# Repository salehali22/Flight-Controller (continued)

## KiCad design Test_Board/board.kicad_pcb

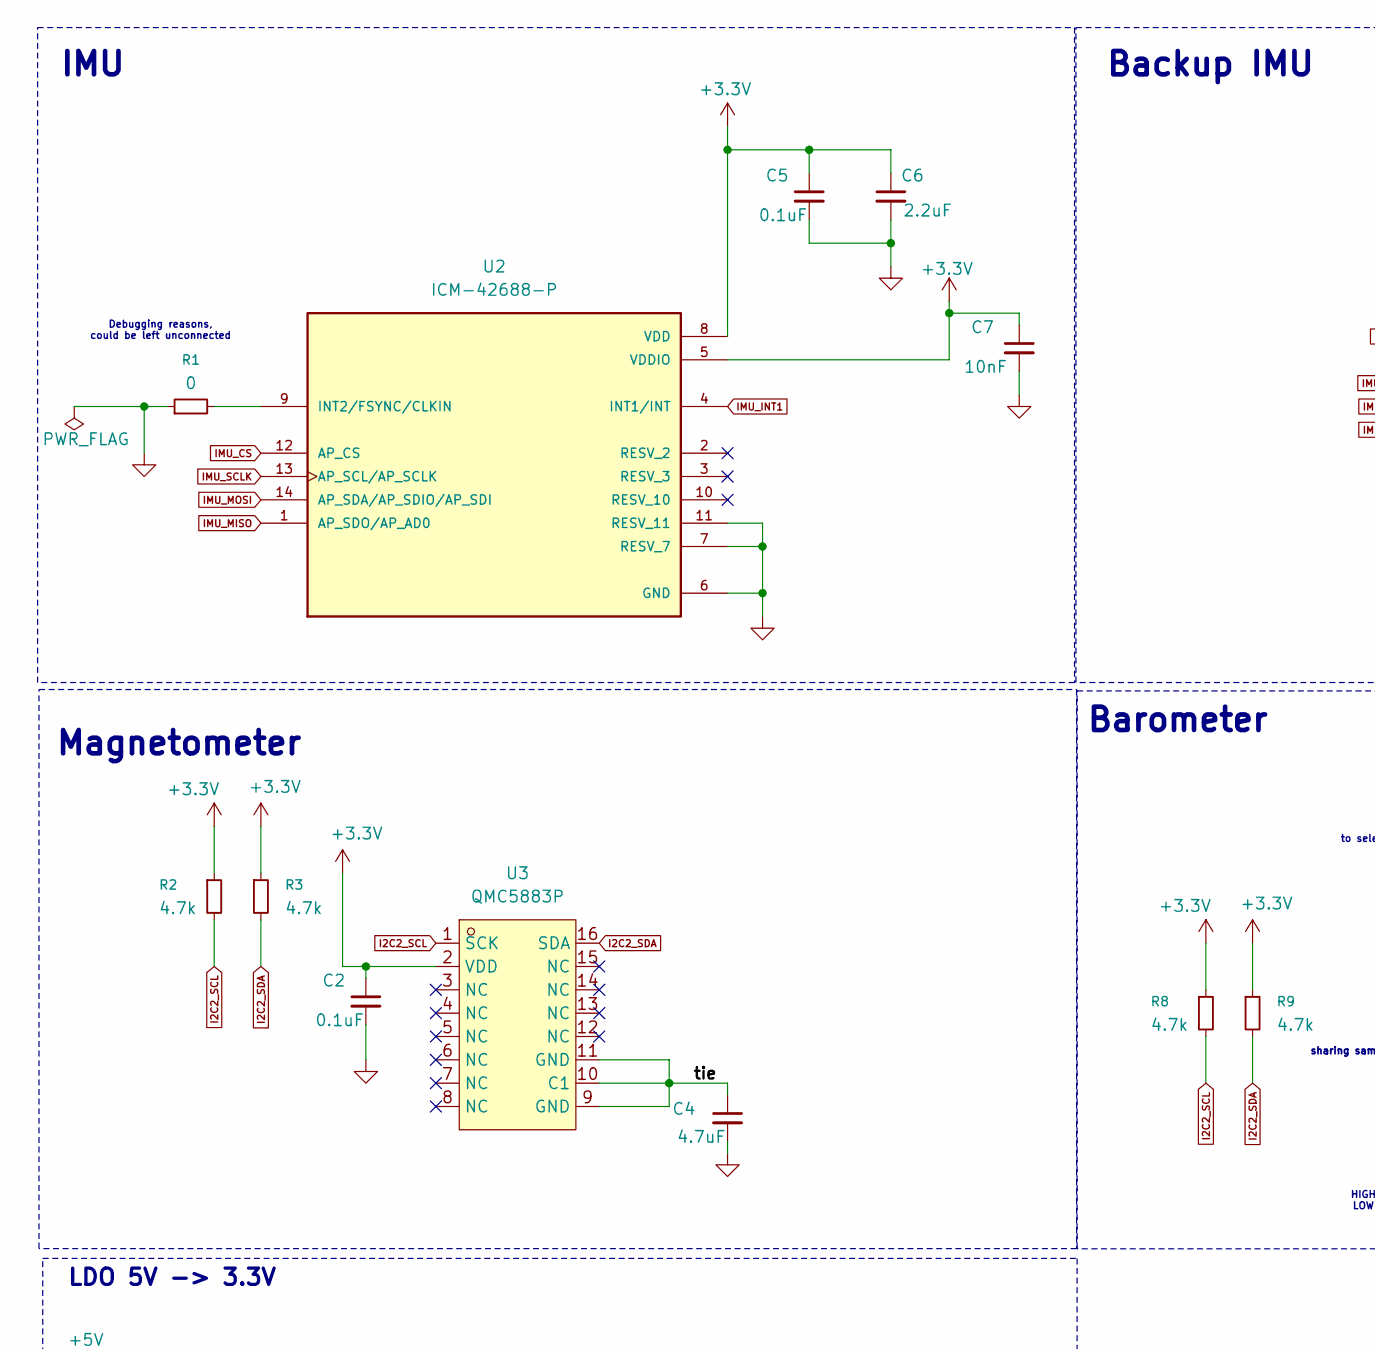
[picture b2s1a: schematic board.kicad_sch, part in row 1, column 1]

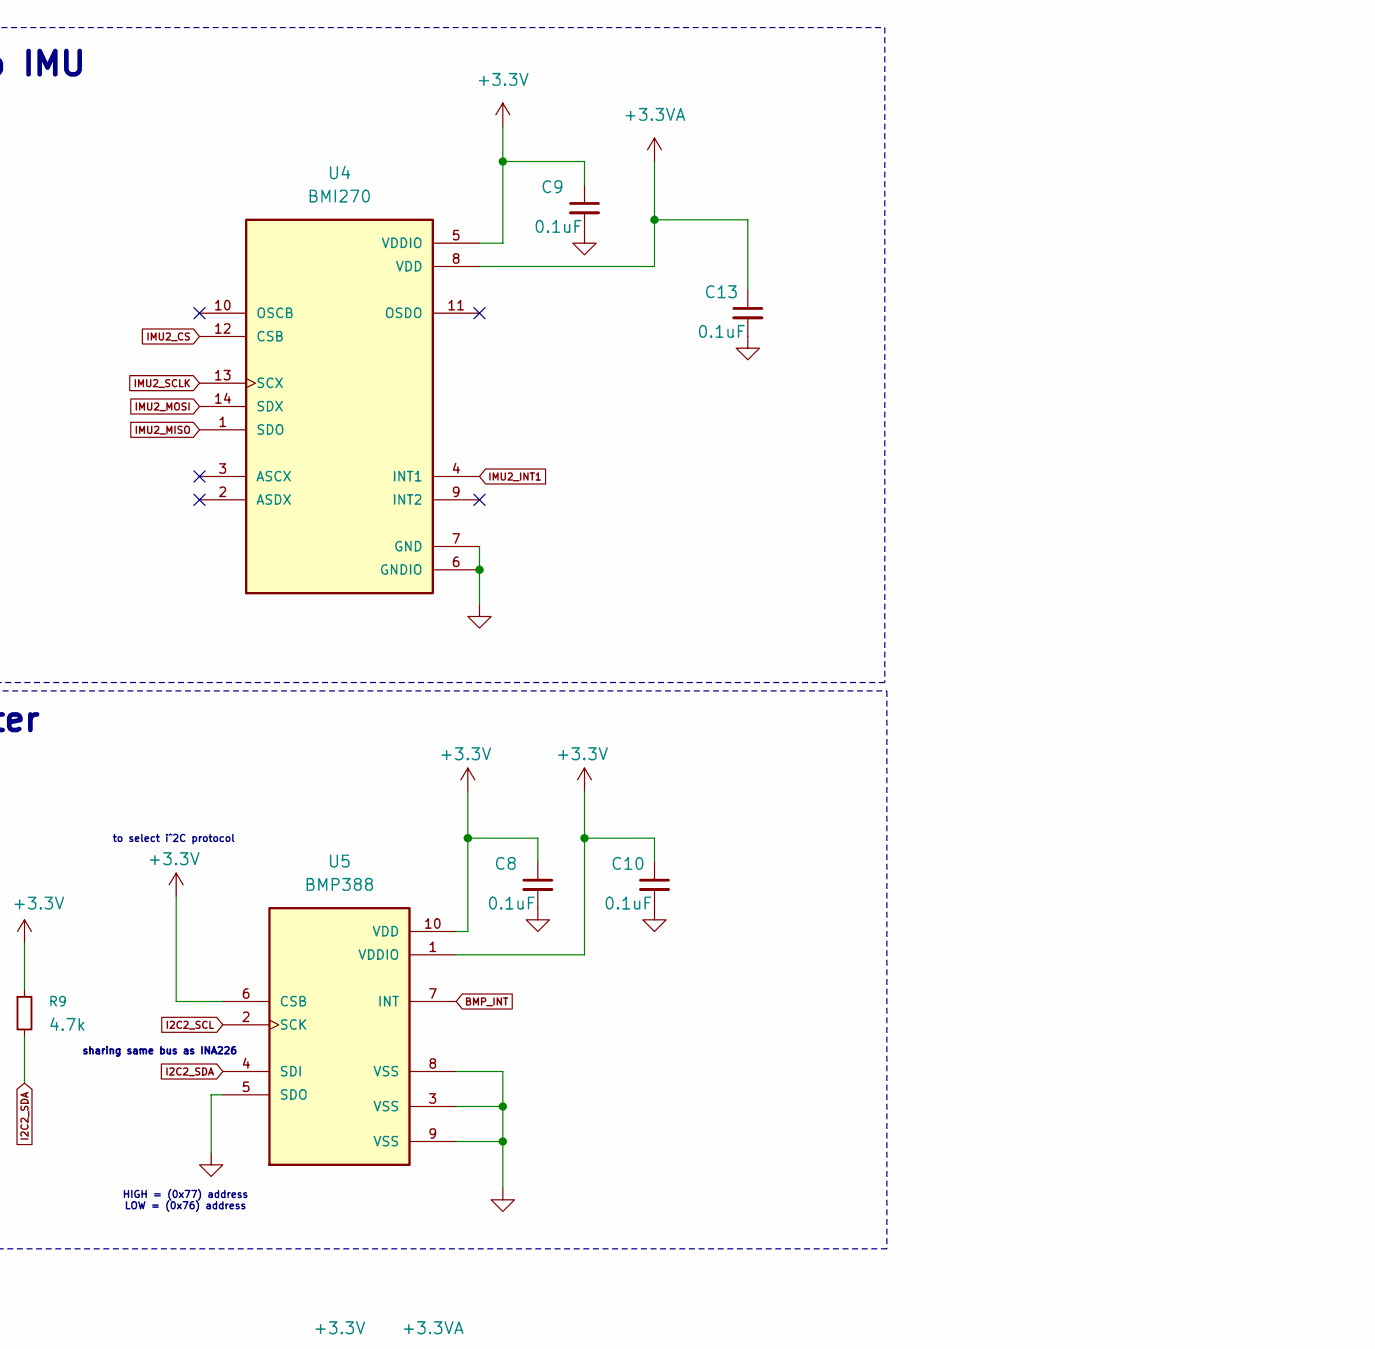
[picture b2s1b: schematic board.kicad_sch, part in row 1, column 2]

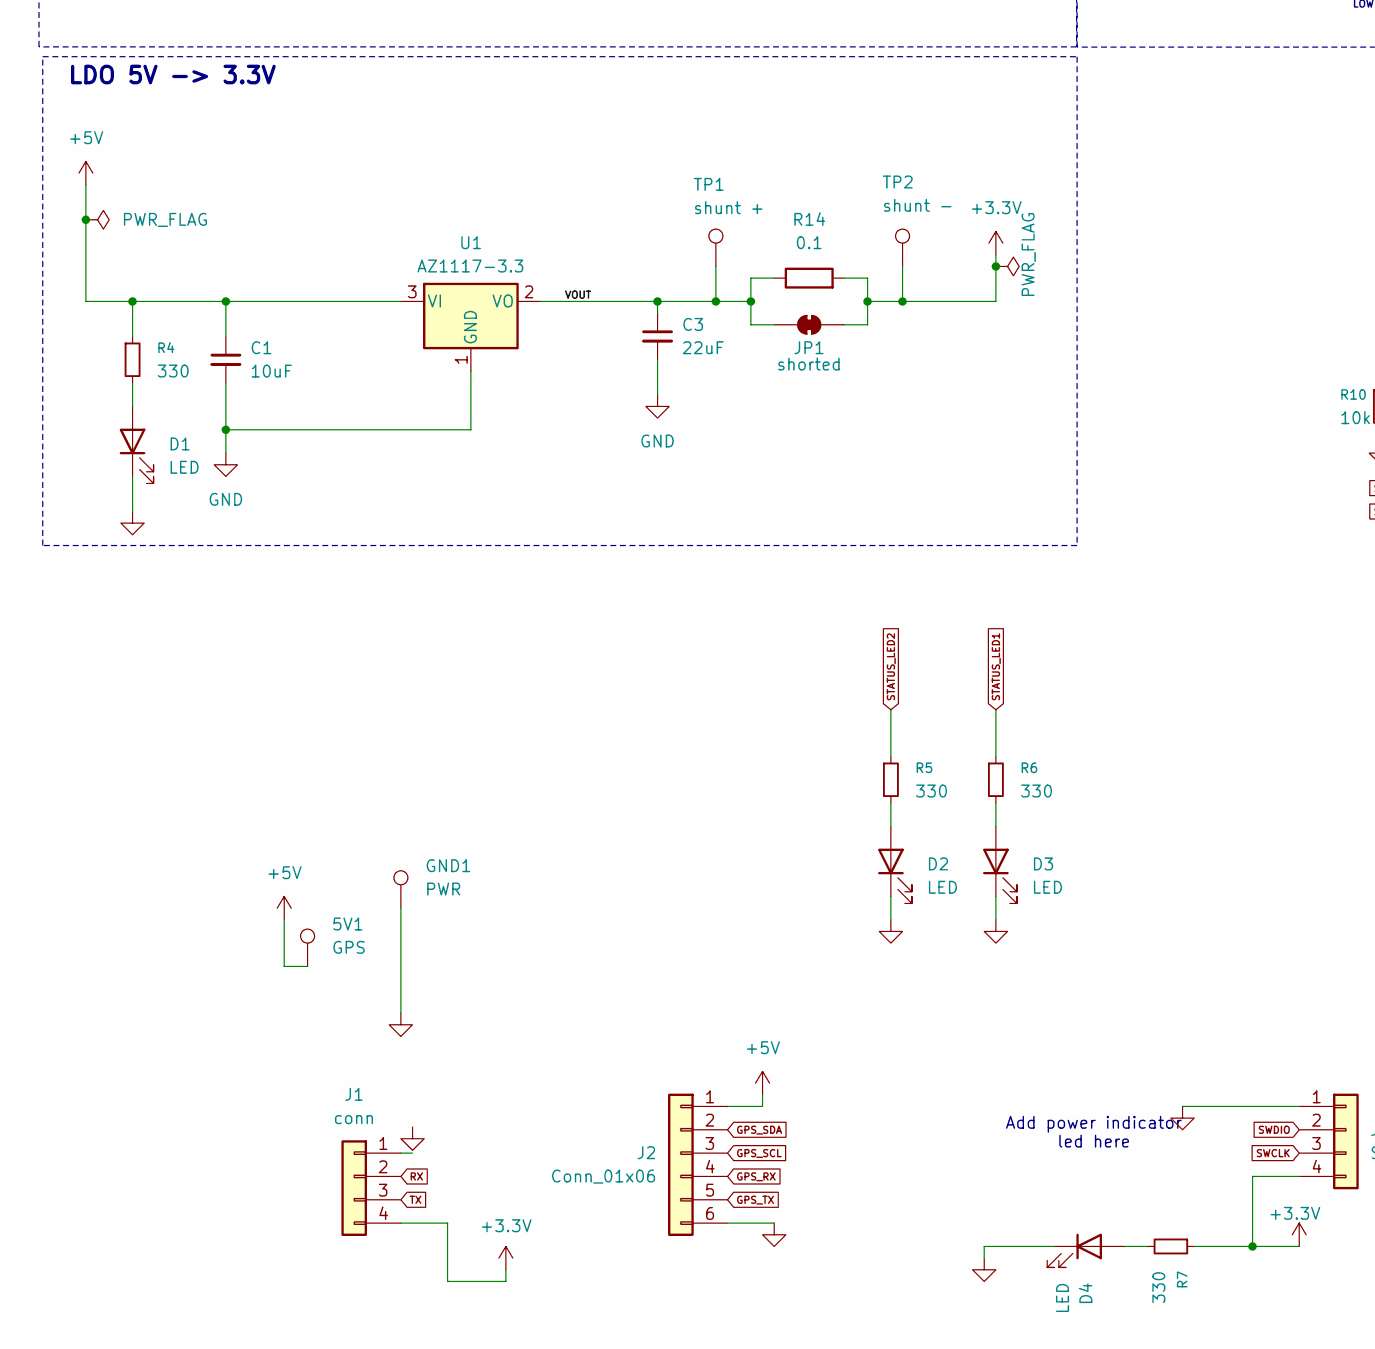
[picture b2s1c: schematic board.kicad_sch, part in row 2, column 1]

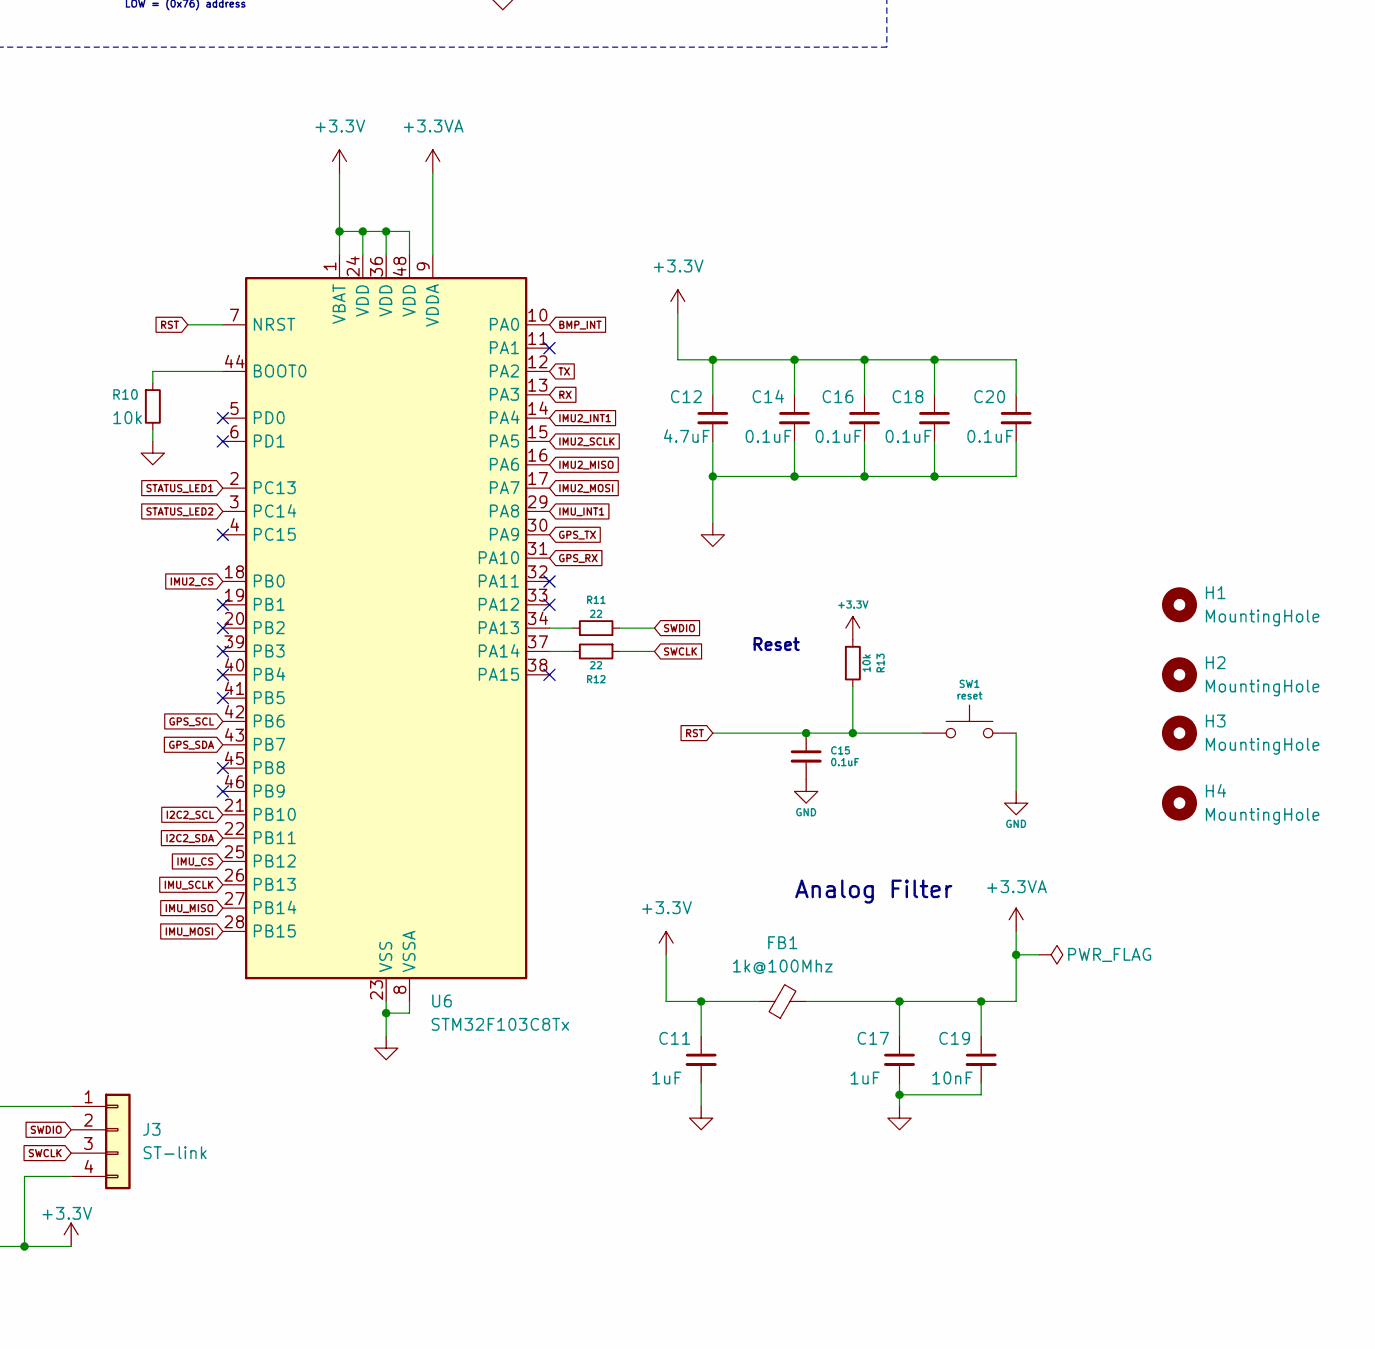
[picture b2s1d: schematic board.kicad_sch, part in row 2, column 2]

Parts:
5V1: GPS; Solderpad
C1: 10uF; C_0603_1608Metric; JLCPCB PART# C19702
C2, C5, C8, C9, C10, C13, C14, C15, C16, C18, C20: 0.1uF; C_0603_1608Metric; JLCPCB PART# C14663
C3: 22uF; C_0603_1608Metric; JLCPCB PART# C86295
C4, C12: 4.7uF; C_0603_1608Metric; JLCPCB PART# C1705
C6: 2.2uF; C_0603_1608Metric; JLCPCB PART# C23630
C7, C19: 10nF; C_0603_1608Metric; JLCPCB PART# C100042
C11, C17: 1uF; C_0603_1608Metric; JLCPCB PART# C15849
D1, D2, D3, D4: LED; LED_0805_2012Metric; JLCPCB PART# C20608785
FB1: 1k@100Mhz; L_0603_1608Metric; JLCPCB PART# C44838
GND1: PWR; Solderpad
H1, H2, H3, H4: MountingHole; MountingHole_2.2mm_M2_Pad_Via
J1: conn; JST_EH_B4B-EH-A_1x04_P2.50mm_Vertical
J2: Conn_01x06; PinHeader_1x06_P2.54mm_Vertical
J3: ST-link; PinHeader_1x04_P2.54mm_Horizontal
JP1: shorted; SolderJumper-2_P1.3mm_Bridged_Pad1.0x1.5mm
R1: 0; R_0603_1608Metric; JLCPCB PART# C95177
R2, R3, R8, R9: 4.7k; R_0603_1608Metric; JLCPCB PART# C2904521
R4, R5, R6, R7: 330; R_0603_1608Metric; JLCPCB PART# C105881
R10, R13: 10k; R_0603_1608Metric; JLCPCB PART# C98220
R11, R12: 22; R_0603_1608Metric; JLCPCB PART# C107701
R14: 0.1; R_2512_6332Metric_Pad1.40x3.35mm_HandSolder
SW1: reset; SW_Push_SPST_NO_Alps_SKRK; JLCPCB PART# C115357
TP1: shunt +; Solderpad
TP2: shunt -; Solderpad
U1: AZ1117-3.3; SOT-223; JLCPCB PART# C108495
U2: ICM-42688-P; PQFN50P300X250X97-14N; PARTREV 1.2
U3: QMC5883P; LCSC Part C2847467
U4: BMI270; XDCR_BMI270; JLCPCB PART# C2836813
U5: BMP388; PQFN50P200X200X80-10N; PARTREV 1.1; JLCPCB PART# C779278
U6: STM32F103C8Tx; LQFP-48_7x7mm_P0.5mm; JLCPCB PART# C8734

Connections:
+3.3V: C2.1, C5.1, C6.1, C7.1, C8.1, C9.1, C10.1, C11.1, C12.1, C14.1, C16.1, C18.1, C20.1, FB1.1, J1.4, J3.4, JP1.2 (B), R2.1, R3.1, R7.1, R8.1, R9.1, R13.1, R14.2, TP2.1, U2.5 (VDDIO), U2.8 (VDD), U3.2 (VDD), U4.5 (VDDIO), U5.1 (VDDIO), U5.6 (CSB), U5.10 (VDD), U6.1 (VBAT), U6.24 (VDD), U6.36 (VDD), U6.48 (VDD)
+3.3VA: C13.1, C17.1, C19.1, FB1.2, U4.8 (VDD), U6.9 (VDDA)
+5V: 5V1.1, C1.1, J2.1, R4.1, U1.3 (VI)
/VOUT: C3.1, JP1.1 (A), R14.1, TP1.1, U1.2 (VO)
/tie: C4.1, U3.9 (GND), U3.10 (C1), U3.11 (GND)
BMP_INT: U5.7 (INT), U6.10 (PA0)
GND: C1.2, C2.2, C3.2, C4.2, C5.2, C6.2, C7.2, C8.2, C9.2, C10.2, C11.2, C12.2, C13.2, C14.2, C15.2, C16.2, C17.2, C18.2, C19.2, C20.2, D1.1 (K), D2.1 (K), D3.1 (K), D4.1 (K), GND1.1, J2.6, J3.1, R1.1, R10.2, SW1.2, U1.1 (GND), U2.6 (GND), U2.7 (RESV_7), U2.11 (RESV_11), U4.6 (GNDIO), U4.7 (GND), U5.3 (VSS), U5.5 (SDO), U5.8 (VSS), U5.9 (VSS), U6.8 (VSSA), U6.23 (VSS), U6.35 (VSS), U6.47 (VSS)
GPS_RX: J2.4, U6.31 (PA10)
GPS_SCL: J2.3, U6.42 (PB6)
GPS_SDA: J2.2, U6.43 (PB7)
GPS_TX: J2.5, U6.30 (PA9)
I2C2_SCL: R2.2, R8.2, U3.1 (SCK), U5.2 (SCK), U6.21 (PB10)
I2C2_SDA: R3.2, R9.2, U3.16 (SDA), U5.4 (SDI), U6.22 (PB11)
IMU2_CS: U4.12 (CSB), U6.18 (PB0)
IMU2_INT1: U4.4 (INT1), U6.14 (PA4)
IMU2_MISO: U4.1 (SDO), U6.16 (PA6)
IMU2_MOSI: U4.14 (SDX), U6.17 (PA7)
IMU2_SCLK: U4.13 (SCX), U6.15 (PA5)
IMU_CS: U2.12 (AP_CS), U6.25 (PB12)
IMU_INT1: U2.4 (INT1/INT), U6.29 (PA8)
IMU_MISO: U2.1 (AP_SDO/AP_AD0), U6.27 (PB14)
IMU_MOSI: U2.14 (AP_SDA/AP_SDIO/AP_SDI), U6.28 (PB15)
IMU_SCLK: U2.13 (AP_SCL/AP_SCLK), U6.26 (PB13)
unnamed: D1.2 (A), R4.2
unnamed: D2.2 (A), R5.2
unnamed: D3.2 (A), R6.2
unnamed: D4.2 (A), R7.2
unnamed: R1.2, U2.9 (INT2/FSYNC/CLKIN)
unnamed: R10.1, U6.44 (BOOT0)
unnamed: R11.1, U6.34 (PA13)
unnamed: R12.2, U6.37 (PA14)
RST: C15.1, R13.2, SW1.1, U6.7 (NRST)
RX: J1.2, U6.13 (PA3)
STATUS_LED1: R6.1, U6.2 (PC13)
STATUS_LED2: R5.1, U6.3 (PC14)
SWCLK: J3.3, R12.1
SWDIO: J3.2, R11.2
TX: J1.3, U6.12 (PA2)

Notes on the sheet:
Analog Filter
Add power indicator led here
Backup IMU
Debugging reasons, could be left unconnected
to select i^2C protocol
Reset
Barometer
LDO 5V -> 3.3V
IMU
HIGH = (0x77) address LOW = (0x76) address
Magnetometer
sharing same bus as INA226

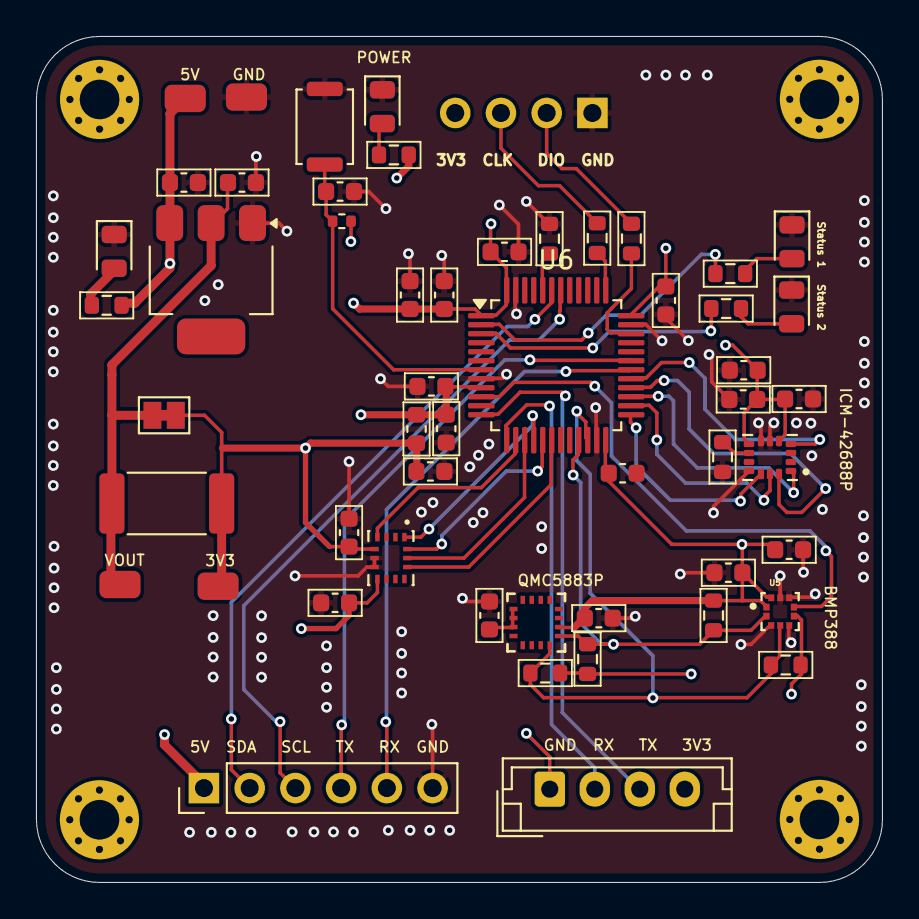
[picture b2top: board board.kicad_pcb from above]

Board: 4 copper layers, 47.0 x 47.0 mm, 58 parts (1 on the bottom side), 38 nets.

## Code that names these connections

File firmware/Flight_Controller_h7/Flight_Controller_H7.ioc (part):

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Mcu.Name=STM32H743VITx
Mcu.Package=LQFP100
Mcu.UserName=STM32H743VITx
PA0.GPIOParameters=PinAttribute
PA0.Mode=Asynchronous
PA0.PinAttribute=Free
PA0.Signal=UART4_TX
PA1.GPIOParameters=GPIO_Label,PinAttribute
PA1.GPIO_Label=DJI_SBUS
PA1.Mode=Asynchronous
PA1.PinAttribute=Free
PA1.Signal=UART4_RX
PA11.GPIOParameters=PinAttribute
PA11.Mode=Device_Only
PA11.PinAttribute=Free
PA11.Signal=USB_OTG_FS_DM
PA12.GPIOParameters=PinAttribute
PA12.Mode=Device_Only
PA12.PinAttribute=Free
PA12.Signal=USB_OTG_FS_DP
PA13\ (JTMS/SWDIO).GPIOParameters=PinAttribute
PA13\ (JTMS/SWDIO).Mode=Serial_Wire
PA13\ (JTMS/SWDIO).PinAttribute=Free
PA13\ (JTMS/SWDIO).Signal=DEBUG_JTMS-SWDIO
PA14\ (JTCK/SWCLK).GPIOParameters=PinAttribute
PA14\ (JTCK/SWCLK).Mode=Serial_Wire
PA14\ (JTCK/SWCLK).PinAttribute=Free
PA14\ (JTCK/SWCLK).Signal=DEBUG_JTCK-SWCLK
PA2.GPIOParameters=GPIO_Label,PinAttribute
PA2.GPIO_Label=VTX_TX
PA2.Mode=Asynchronous
PA2.PinAttribute=Free
PA2.Signal=USART2_TX
PA3.GPIOParameters=GPIO_Label,PinAttribute
PA3.GPIO_Label=VTX_RX
PA3.Mode=Asynchronous
PA3.PinAttribute=Free
PA3.Signal=USART2_RX
PA4.GPIOParameters=GPIO_Label,PinAttribute
PA4.GPIO_Label=FLASH_CS
PA4.PinAttribute=Free
PA4.Signal=GPIO_Output
PA5.GPIOParameters=GPIO_Label,PinAttribute
PA5.GPIO_Label=FLASH_SCK
PA5.Mode=Full_Duplex_Master
PA5.PinAttribute=Free
PA5.Signal=SPI1_SCK
PA6.GPIOParameters=GPIO_Label,PinAttribute
PA6.GPIO_Label=FLASH_MISO
PA6.Mode=Full_Duplex_Master
PA6.PinAttribute=Free
PA6.Signal=SPI1_MISO
PA7.GPIOParameters=GPIO_Label,PinAttribute
PA7.GPIO_Label=FLASH_MOSI
PA7.Mode=Full_Duplex_Master
PA7.PinAttribute=Free
PA7.Signal=SPI1_MOSI
PB0.GPIOParameters=PinState,GPIO_Label,PinAttribute
PB0.GPIO_Label=STATUS_LED_1
PB0.PinAttribute=Free
PB0.PinState=GPIO_PIN_SET
PB0.Signal=GPIO_Output
PB1.GPIOParameters=GPIO_Label,PinAttribute
PB1.GPIO_Label=BMP_INT1
PB1.PinAttribute=Free
PB1.Signal=GPXTI1
PB10.GPIOParameters=PinAttribute
PB10.Mode=I2C
PB10.PinAttribute=Free
PB10.Signal=I2C2_SCL
PB11.GPIOParameters=PinAttribute
PB11.Mode=I2C
PB11.PinAttribute=Free
PB11.Signal=I2C2_SDA
PB12.GPIOParameters=GPIO_Label,PinAttribute
PB12.GPIO_Label=TELEMETRY_RX
PB12.Mode=Asynchronous
PB12.PinAttribute=Free
PB12.Signal=UART5_RX
PB13.GPIOParameters=GPIO_Label,PinAttribute
PB13.GPIO_Label=TELEMETRY_TX
PB13.Mode=Asynchronous
PB13.PinAttribute=Free
PB13.Signal=UART5_TX
PB14.GPIOParameters=GPIO_Label,PinAttribute
PB14.GPIO_Label=Expansion_TX
PB14.Mode=Asynchronous
PB14.PinAttribute=Free
PB14.Signal=USART1_TX
PB15.GPIOParameters=GPIO_Label,PinAttribute
PB15.GPIO_Label=Expansion_RX
PB15.Mode=Asynchronous
PB15.PinAttribute=Free
PB15.Signal=USART1_RX
PB3\ (JTDO/TRACESWO).GPIOParameters=GPIO_Label,PinAttribute
PB3\ (JTDO/TRACESWO).GPIO_Label=IMU2_SCLK
PB3\ (JTDO/TRACESWO).Mode=Full_Duplex_Master
PB3\ (JTDO/TRACESWO).PinAttribute=Free
PB3\ (JTDO/TRACESWO).Signal=SPI6_SCK
PB4\ (NJTRST).GPIOParameters=GPIO_Label,PinAttribute
PB4\ (NJTRST).GPIO_Label=IMU2_MISO
PB4\ (NJTRST).Mode=Full_Duplex_Master
PB4\ (NJTRST).PinAttribute=Free
PB4\ (NJTRST).Signal=SPI6_MISO
PB5.GPIOParameters=GPIO_Label,PinAttribute
PB5.GPIO_Label=IMU2_MOSI
PB5.Mode=Full_Duplex_Master
PB5.PinAttribute=Free
PB5.Signal=SPI6_MOSI
PB6.GPIOParameters=GPIO_Label,PinAttribute
PB6.GPIO_Label=GPS_SCL
PB6.Mode=I2C
PB6.PinAttribute=Free
PB6.Signal=I2C4_SCL
PB7.GPIOParameters=GPIO_Label,PinAttribute
PB7.GPIO_Label=GPS_SDA
PB7.Mode=I2C
PB7.PinAttribute=Free
PB7.Signal=I2C4_SDA
PB8.GPIOParameters=PinAttribute
PB8.Mode=I2C
PB8.PinAttribute=Free
PB8.Signal=I2C1_SCL
PB9.GPIOParameters=PinAttribute
PB9.Mode=I2C
PB9.PinAttribute=Free
PB9.Signal=I2C1_SDA
PC1.GPIOParameters=GPIO_Label,PinAttribute
PC1.GPIO_Label=ADC_VOLTAGE
PC1.PinAttribute=Free
PC1.Signal=ADCx_INP11
PC10.GPIOParameters=GPIO_Label,PinAttribute
PC10.GPIO_Label=IMU_SCLK
PC10.Mode=Full_Duplex_Master
PC10.PinAttribute=Free
PC10.Signal=SPI3_SCK
PC11.GPIOParameters=GPIO_Label,PinAttribute
PC11.GPIO_Label=IMU_MISO
PC11.Mode=Full_Duplex_Master
PC11.PinAttribute=Free
PC11.Signal=SPI3_MISO
PC12.GPIOParameters=GPIO_Label,PinAttribute
PC12.GPIO_Label=IMU_MOSI
PC12.Mode=Full_Duplex_Master
PC12.PinAttribute=Free
PC12.Signal=SPI3_MOSI
PC13.GPIOParameters=GPIO_Label,PinAttribute
PC13.GPIO_Label=OSD_CS
PC13.PinAttribute=Free
PC13.Signal=GPIO_Output
PC3_C.GPIOParameters=GPIO_Label,PinAttribute
PC3_C.GPIO_Label=ADC_CURR
PC3_C.Mode=IN1-Single-Ended
PC3_C.PinAttribute=Free
PC3_C.Signal=ADC3_INP1
PC5.GPIOParameters=PinState,GPIO_Label,PinAttribute
PC5.GPIO_Label=STATUS_LED_2
PC5.PinAttribute=Free
PC5.PinState=GPIO_PIN_SET
PC5.Signal=GPIO_Output
PC6.GPIOParameters=GPIO_Label,PinAttribute
PC6.GPIO_Label=M1
PC6.PinAttribute=Free
PC6.Signal=S_TIM8_CH1
PC7.GPIOParameters=GPIO_Label,PinAttribute
PC7.GPIO_Label=M2
PC7.PinAttribute=Free
PC7.Signal=S_TIM8_CH2
PC8.GPIOParameters=GPIO_Label,PinAttribute
PC8.GPIO_Label=M3
PC8.PinAttribute=Free
PC8.Signal=S_TIM8_CH3
PC9.GPIOParameters=GPIO_Label,PinAttribute
PC9.GPIO_Label=M4
PC9.PinAttribute=Free
PC9.Signal=S_TIM8_CH4
PD0.GPIOParameters=PinAttribute
PD0.Mode=FDCAN_Activate
PD0.PinAttribute=Free
PD0.Signal=FDCAN1_RX
PD1.GPIOParameters=PinAttribute
PD1.Mode=FDCAN_Activate
PD1.PinAttribute=Free
PD1.Signal=FDCAN1_TX
PD12.GPIOParameters=GPIO_Label,PinAttribute
PD12.GPIO_Label=S1
PD12.PinAttribute=Free
PD12.Signal=S_TIM4_CH1
PD13.GPIOParameters=GPIO_Label,PinAttribute
PD13.GPIO_Label=S2
PD13.PinAttribute=Free
PD13.Signal=S_TIM4_CH2
PD14.GPIOParameters=GPIO_Label,PinAttribute
PD14.GPIO_Label=S3
PD14.PinAttribute=Free
PD14.Signal=S_TIM4_CH3
PD15.GPIOParameters=GPIO_Label,PinAttribute
PD15.GPIO_Label=S4
PD15.PinAttribute=Free
PD15.Signal=S_TIM4_CH4
PD2.GPIOParameters=GPIO_Label,PinAttribute
PD2.GPIO_Label=IMU_INT1
PD2.PinAttribute=Free
PD2.Signal=GPXTI2
PD3.GPIOParameters=GPIO_Label,PinAttribute
PD3.GPIO_Label=IMU_CS
PD3.PinAttribute=Free
PD3.Signal=GPIO_Output
PD7.GPIOParameters=GPIO_Label,PinAttribute
PD7.GPIO_Label=IMU2_CS
PD7.PinAttribute=Free
PD7.Signal=GPIO_Output
PD8.GPIOParameters=GPIO_Label,PinAttribute
PD8.GPIO_Label=WIFI/RC_TX
PD8.Mode=Asynchronous
PD8.PinAttribute=Free
PD8.Signal=USART3_TX
PD9.GPIOParameters=GPIO_Label,PinAttribute
PD9.GPIO_Label=WIFI/RC_RX
PD9.Mode=Asynchronous
PD9.PinAttribute=Free
PD9.Signal=USART3_RX
PE0.GPIOParameters=GPIO_Label,PinAttribute
PE0.GPIO_Label=GPS_RX
PE0.Mode=Asynchronous
PE0.PinAttribute=Free
PE0.Signal=UART8_RX
PE1.GPIOParameters=GPIO_Label,PinAttribute
PE1.GPIO_Label=GPS_TX
PE1.Mode=Asynchronous
PE1.PinAttribute=Free
PE1.Signal=UART8_TX
PE11.GPIOParameters=GPIO_Label,PinAttribute
PE11.GPIO_Label=M6
PE11.PinAttribute=Free
PE11.Signal=S_TIM1_CH2
PE13.GPIOParameters=GPIO_Label,PinAttribute
PE13.GPIO_Label=M7
PE13.PinAttribute=Free
PE13.Signal=S_TIM1_CH3
PE14.GPIOParameters=GPIO_Label,PinAttribute
PE14.GPIO_Label=M8
PE14.PinAttribute=Free
PE14.Signal=S_TIM1_CH4
PE2.GPIOParameters=GPIO_Label,PinAttribute
PE2.GPIO_Label=OSD_SCK
PE2.Mode=Full_Duplex_Master
PE2.PinAttribute=Free
PE2.Signal=SPI4_SCK
PE4.GPIOParameters=GPIO_Label,PinAttribute
PE4.GPIO_Label=IMU2_INT
PE4.PinAttribute=Free
PE4.Signal=GPXTI4
PE5.GPIOParameters=GPIO_Label,PinAttribute
PE5.GPIO_Label=OSD_MISO
PE5.Mode=Full_Duplex_Master
PE5.PinAttribute=Free
PE5.Signal=SPI4_MISO
PE6.GPIOParameters=GPIO_Label,PinAttribute
PE6.GPIO_Label=OSD_MOSI
PE6.Mode=Full_Duplex_Master
PE6.PinAttribute=Free
PE6.Signal=SPI4_MOSI
PE7.GPIOParameters=GPIO_Label,PinAttribute
PE7.GPIO_Label=DJI_RX
PE7.Mode=Asynchronous
PE7.PinAttribute=Free
PE7.Signal=UART7_RX
PE8.GPIOParameters=GPIO_Label,PinAttribute
PE8.GPIO_Label=DJI_TX
PE8.Mode=Asynchronous
PE8.PinAttribute=Free
PE8.Signal=UART7_TX
PE9.GPIOParameters=GPIO_Label,PinAttribute
PE9.GPIO_Label=M5
PE9.PinAttribute=Free
PE9.Signal=S_TIM1_CH1
PH0-OSC_IN\ (PH0).GPIOParameters=PinAttribute
PH0-OSC_IN\ (PH0).Mode=HSE-External-Clock-Source
PH0-OSC_IN\ (PH0).PinAttribute=Free
PH0-OSC_IN\ (PH0).Signal=RCC_OSC_IN
RCC.HSE_VALUE=8000000
RCC.SYSCLKFreq_VALUE=240000000
RCC.SYSCLKSource=RCC_SYSCLKSOURCE_PLLCLK
board=custom

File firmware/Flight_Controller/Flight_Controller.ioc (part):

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Mcu.Name=STM32F722R(C-E)Tx
Mcu.Package=LQFP64
Mcu.UserName=STM32F722RETx
PA0-WKUP.GPIOParameters=GPIO_Label
PA0-WKUP.GPIO_Label=WIFI_TX
PA0-WKUP.Mode=Asynchronous
PA0-WKUP.Signal=UART4_TX
PA1.GPIOParameters=GPIO_Label
PA1.GPIO_Label=WIFI_RX
PA1.Mode=Asynchronous
PA1.Signal=UART4_RX
PA10.GPIOParameters=GPIO_Label
PA10.GPIO_Label=RC_Receiver_RX
PA10.Mode=Asynchronous
PA10.Signal=USART1_RX
PA11.Mode=Device_Only
PA11.Signal=USB_OTG_FS_DM
PA12.Mode=Device_Only
PA12.Signal=USB_OTG_FS_DP
PA13.Mode=Serial_Wire
PA13.Signal=SYS_JTMS-SWDIO
PA14.Mode=Serial_Wire
PA14.Signal=SYS_JTCK-SWCLK
PA2.GPIOParameters=GPIO_Label
PA2.GPIO_Label=GPS_TX
PA2.Mode=Asynchronous
PA2.Signal=USART2_TX
PA3.GPIOParameters=GPIO_Label
PA3.GPIO_Label=GPS_RX
PA3.Mode=Asynchronous
PA3.Signal=USART2_RX
PA4.GPIOParameters=GPIO_Label
PA4.GPIO_Label=IMU_CS
PA4.Signal=GPIO_Output
PA5.GPIOParameters=GPIO_Label
PA5.GPIO_Label=IMU_SCLK
PA5.Mode=Full_Duplex_Master
PA5.Signal=SPI1_SCK
PA6.GPIOParameters=GPIO_Label
PA6.GPIO_Label=IMU_MISO
PA6.Mode=Full_Duplex_Master
PA6.Signal=SPI1_MISO
PA7.GPIOParameters=GPIO_Label
PA7.GPIO_Label=IMU_MOSI
PA7.Mode=Full_Duplex_Master
PA7.Signal=SPI1_MOSI
PA8.GPIOParameters=GPIO_Label
PA8.GPIO_Label=GPS_SCL
PA8.Mode=I2C
PA8.Signal=I2C3_SCL
PA9.GPIOParameters=GPIO_Label
PA9.GPIO_Label=RC_Receiver_TX
PA9.Mode=Asynchronous
PA9.Signal=USART1_TX
PB0.GPIOParameters=GPIO_Label
PB0.GPIO_Label=ADC_Voltage
PB0.Signal=ADCx_IN8
PB1.GPIOParameters=GPIO_Label
PB1.GPIO_Label=SERVO_3
PB1.Signal=S_TIM3_CH4
PB10.GPIOParameters=GPIO_Label
PB10.GPIO_Label=I2C2_SCL
PB10.Mode=I2C
PB10.Signal=I2C2_SCL
PB11.GPIOParameters=GPIO_Label
PB11.GPIO_Label=I2C2_SDA
PB11.Mode=I2C
PB11.Signal=I2C2_SDA
PB12.GPIOParameters=GPIO_Label
PB12.GPIO_Label=OSD_CS
PB12.Signal=GPIO_Output
PB13.GPIOParameters=GPIO_Label
PB13.GPIO_Label=OSD_SCLK
PB13.Mode=Full_Duplex_Master
PB13.Signal=SPI2_SCK
PB14.GPIOParameters=GPIO_Label
PB14.GPIO_Label=SERVO_2
PB14.Signal=S_TIM12_CH1
PB15.GPIOParameters=GPIO_Label
PB15.GPIO_Label=SERVO_1
PB15.Signal=S_TIM12_CH2
PB2.GPIOParameters=GPIO_Label
PB2.GPIO_Label=FLASH_MOSI
PB2.Mode=Full_Duplex_Master
PB2.Signal=SPI3_MOSI
PB3.GPIOParameters=GPIO_Label
PB3.GPIO_Label=MOTOR_1
PB3.Signal=S_TIM2_CH2
PB4.GPIOParameters=GPIO_Label
PB4.GPIO_Label=MOTOR_2
PB4.Signal=S_TIM3_CH1
PB5.GPIOParameters=GPIO_Label
PB5.GPIO_Label=MOTOR_3
PB5.Signal=S_TIM3_CH2
PB6.GPIOParameters=GPIO_Label
PB6.GPIO_Label=MOTOR_4
PB6.Signal=S_TIM4_CH1
PB7.GPIOParameters=GPIO_Label
PB7.GPIO_Label=MOTOR_5
PB7.Signal=S_TIM4_CH2
PB8.GPIOParameters=GPIO_Label
PB8.GPIO_Label=QMC_SCL
PB8.Mode=I2C
PB8.Signal=I2C1_SCL
PB9.GPIOParameters=GPIO_Label
PB9.GPIO_Label=QMC_SDA
PB9.Mode=I2C
PB9.Signal=I2C1_SDA
PC0.GPIOParameters=GPIO_Label
PC0.GPIO_Label=STATUS_LED_3
PC0.Signal=GPIO_Output
PC1.GPIOParameters=GPIO_Label
PC1.GPIO_Label=OSD_MOSI
PC1.Mode=Full_Duplex_Master
PC1.Signal=SPI2_MOSI
PC10.GPIOParameters=GPIO_Label
PC10.GPIO_Label=FLASH_SCK
PC10.Mode=Full_Duplex_Master
PC10.Signal=SPI3_SCK
PC11.GPIOParameters=GPIO_Label
PC11.GPIO_Label=FLASH_MISO
PC11.Mode=Full_Duplex_Master
PC11.Signal=SPI3_MISO
PC12.GPIOParameters=GPIO_Label
PC12.GPIO_Label=FLASH_CS
PC12.Signal=GPIO_Output
PC13.GPIOParameters=GPIO_Label
PC13.GPIO_Label=INA226_ALERT
PC13.Signal=GPIO_Input
PC14-OSC32_IN.GPIOParameters=GPIO_Label
PC14-OSC32_IN.GPIO_Label=STATUS_LED_1
PC14-OSC32_IN.Signal=GPIO_Output
PC15-OSC32_OUT.GPIOParameters=GPIO_Label
PC15-OSC32_OUT.GPIO_Label=STATUS_LED_2
PC15-OSC32_OUT.Signal=GPIO_Output
PC2.GPIOParameters=GPIO_Label
PC2.GPIO_Label=OSD_MISO
PC2.Mode=Full_Duplex_Master
PC2.Signal=SPI2_MISO
PC3.GPIOParameters=GPIO_Label
PC3.GPIO_Label=BMP_INT
PC3.Signal=GPXTI3
PC6.GPIOParameters=GPIO_Label
PC6.GPIO_Label=Telemetry_TX
PC6.Mode=Asynchronous
PC6.Signal=USART6_TX
PC7.GPIOParameters=GPIO_Label
PC7.GPIO_Label=Telemetry_RX
PC7.Mode=Asynchronous
PC7.Signal=USART6_RX
PC8.GPIOParameters=GPIO_Label
PC8.GPIO_Label=IMU_INT
PC8.Signal=GPXTI8
PC9.GPIOParameters=GPIO_Label
PC9.GPIO_Label=GPS_SDA
PC9.Mode=I2C
PC9.Signal=I2C3_SDA
PH0-OSC_IN.Mode=HSE-External-Clock-Source
PH0-OSC_IN.Signal=RCC_OSC_IN
PH1-OSC_OUT.Mode=HSE-External-Clock-Source
PH1-OSC_OUT.Signal=RCC_OSC_OUT
RCC.HSE_VALUE=25000000
RCC.SYSCLKFreq_VALUE=216000000
RCC.SYSCLKSource=RCC_SYSCLKSOURCE_PLLCLK
board=custom

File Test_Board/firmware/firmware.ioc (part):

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Mcu.Name=STM32F103C(8-B)Tx
Mcu.Package=LQFP48
Mcu.UserName=STM32F103C8Tx
PA0-WKUP.GPIOParameters=GPIO_Label
PA0-WKUP.GPIO_Label=BMP_INT1
PA0-WKUP.Signal=GPXTI0
PA10.GPIOParameters=GPIO_Label
PA10.GPIO_Label=GPS_RX
PA10.Mode=Asynchronous
PA10.Signal=USART1_RX
PA13.Mode=Serial_Wire
PA13.Signal=SYS_JTMS-SWDIO
PA14.Mode=Serial_Wire
PA14.Signal=SYS_JTCK-SWCLK
PA2.GPIOParameters=GPIO_Label
PA2.GPIO_Label=TX
PA2.Mode=Asynchronous
PA2.Signal=USART2_TX
PA3.GPIOParameters=GPIO_Label
PA3.GPIO_Label=RX
PA3.Mode=Asynchronous
PA3.Signal=USART2_RX
PA4.GPIOParameters=GPIO_Label
PA4.GPIO_Label=IMU2_INT1
PA4.Signal=GPXTI4
PA5.GPIOParameters=GPIO_Label
PA5.GPIO_Label=IMU2_SCK
PA5.Mode=Full_Duplex_Master
PA5.Signal=SPI1_SCK
PA6.GPIOParameters=GPIO_Label
PA6.GPIO_Label=IMU2_MISO
PA6.Mode=Full_Duplex_Master
PA6.Signal=SPI1_MISO
PA7.GPIOParameters=GPIO_Label
PA7.GPIO_Label=IMU2_MOSI
PA7.Mode=Full_Duplex_Master
PA7.Signal=SPI1_MOSI
PA8.GPIOParameters=GPIO_Label
PA8.GPIO_Label=IMU_INT1
PA8.Signal=GPXTI8
PA9.GPIOParameters=GPIO_Label
PA9.GPIO_Label=GPS_TX
PA9.Mode=Asynchronous
PA9.Signal=USART1_TX
PB0.GPIOParameters=PinState,GPIO_Label
PB0.GPIO_Label=IMU2_CS
PB0.PinState=GPIO_PIN_SET
PB0.Signal=GPIO_Output
PB10.Mode=I2C
PB10.Signal=I2C2_SCL
PB11.Mode=I2C
PB11.Signal=I2C2_SDA
PB12.GPIOParameters=PinState,GPIO_Label
PB12.GPIO_Label=IMU_CS
PB12.PinState=GPIO_PIN_SET
PB12.Signal=GPIO_Output
PB13.GPIOParameters=GPIO_Label
PB13.GPIO_Label=IMU_SCK
PB13.Mode=Full_Duplex_Master
PB13.Signal=SPI2_SCK
PB14.GPIOParameters=GPIO_Label
PB14.GPIO_Label=IMU_MISO
PB14.Mode=Full_Duplex_Master
PB14.Signal=SPI2_MISO
PB15.GPIOParameters=GPIO_Label
PB15.GPIO_Label=IMU_MOSI
PB15.Mode=Full_Duplex_Master
PB15.Signal=SPI2_MOSI
PB6.GPIOParameters=GPIO_Label
PB6.GPIO_Label=GPS_SCL
PB6.Mode=I2C
PB6.Signal=I2C1_SCL
PB7.GPIOParameters=GPIO_Label
PB7.GPIO_Label=GPS_SDA
PB7.Mode=I2C
PB7.Signal=I2C1_SDA
PC13-TAMPER-RTC.GPIOParameters=PinState,GPIO_Label
PC13-TAMPER-RTC.GPIO_Label=STATUS_LED1
PC13-TAMPER-RTC.PinState=GPIO_PIN_SET
PC13-TAMPER-RTC.Signal=GPIO_Output
PC14-OSC32_IN.GPIOParameters=PinState,GPIO_Label
PC14-OSC32_IN.GPIO_Label=STATUS_LED2
PC14-OSC32_IN.PinState=GPIO_PIN_SET
PC14-OSC32_IN.Signal=GPIO_Output
RCC.SYSCLKFreq_VALUE=24000000
RCC.SYSCLKSource=RCC_SYSCLKSOURCE_PLLCLK
board=custom

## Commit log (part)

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2025-11-12 updated the software on esp32. Sample rate set to 100hz.
2025-11-12 Replaced uC_code with IMU_uC PlatformIO project
2025-11-12 Add IMU_uC project and update IMU_testing.py
2025-11-13 updated interface
2025-11-13 this commit adds the Hardware files
2025-11-13 clean repo
2025-11-13 this commit adds Hardware Folder
2025-11-13 GUI update and complementary filter fix
2025-11-13 Organize IMU code into tools directory
2025-11-14 this commit updates MCU shematics, Flash memory and Magnetometer
2025-11-14 This commit completes MCU and Crystals caps calculations
2025-11-14 updated the evaluation tool
2025-11-14 added modes and fixed some bugs in IMU testings
2025-11-15 added statistics calculations in timed tests
2025-11-15 This commit adds connectors in the schematics
2025-11-15 export reworked, improved frequency
2025-11-16 This commit changes the MCU and adds backup IMU
2025-11-20 Changed 5V Regulator, pin mapping for ESC and motors
2025-11-23 This commit completes the Schematics
2025-11-23 This commit changes Battery Filtering and Fixes Magnetometer wiring
2025-11-25 This commits adds latest Schematics
2025-11-25 This commit Adds test board
2025-11-25 Added connectors STEP files, edited Schematics and started layout
2025-11-26 This commits updates BOM for Test Board, Changes the Ferrit bead value
2025-11-28 Fixed Peripherals for OSD
2025-11-29 modified shcematics BOOT botton, added connector for VTX, did rough Layout
2025-11-29 changed into 2 LDO's one for the IMU's and one for the rest
2025-11-30 Reformed the Schematics Files, reconfigured MCU pins
2025-12-01 Added Necessary Connectors, pads and comments in the respective file
2025-12-01 Added Digital Airspeed Sensor Connector, Changed the Magnetometer
2025-12-03 added support for Pololu 0J8003 board
2025-12-03 clearing unnecessary net classes in power schematics
2025-12-03 slightly fixed pololu board code
2025-12-05 removed enable pin resistor in 9V/12V regulator and Layout progress
2025-12-05 updated wiring of ESD from USB C
2025-12-09 added magnetometer testing
2025-12-16 Changed to CMOS, layout progress
2025-12-18 added CAN connector
2025-12-27 added firmware drivers for all sensors for the test board
2026-01-14 added initial version of website
2026-01-14 progress layout
2026-01-30 changed hella stuff in firmware plan and hardware pcb layout
2026-01-31 layout progress
2026-02-06 hella shit configured, layout progress
2026-02-07 added zener diode, more layout, Power verificatoin
2026-02-08 more routing and placement
2026-02-09 First iteration layout done
2026-02-10 silkscreen and some routing
2026-02-11 refined the layout
2026-02-19 fixed 5V rail
2026-02-21 fixed connectors
2026-02-21 firmware update
2026-02-22 fixed the reset schematics
2026-02-22 DRC implementation
2026-03-03 started ground station application
2026-03-15 added quatronion filter, CRSF protocol, and PID loops
2026-03-20 gnd station removed for now
2026-03-20 fixed orientation
2026-03-20 orientation fixed
2026-03-21 not imp
2026-03-24 Kicad 10.0 adoption
2026-04-05 corrected vavlues of cap
2026-04-05 Add .gitignore, untrack Hardware/.history
2026-04-06 more tunning
2026-04-07 fixed caps values
2026-04-12 added all drivers and usb CDC, motor mixing still not working
2026-04-18 added 3D step PCB file
2026-04-19 firmware and config tool
2026-05-06 updated the website
2026-06-24 removed Configurator
2026-06-24 removed Hardware Backup
2026-06-24 Cleaned Hardware Folder
2026-06-24 Cleaned Firmware Folder
2026-06-24 removed Test_Board
2026-06-24 Remove testboard folder from repo
2026-06-24 added renders folder
2026-06-24 Remove Test_Board from tracking
2026-06-24 fix git.ignore file
2026-06-26 Adding Config Files and Flashable Firmwares of All three Firmwares
2026-06-28 readme file
2026-06-28 hehe
2026-06-28 Add CERN-OHL-S-2.0 license
2026-06-28 License Fix
2026-06-28 fixed README
2026-06-28 README
2026-06-28 more readme
2026-06-29 README fine tuning
